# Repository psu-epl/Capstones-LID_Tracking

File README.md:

Capstones-LID_Tracking
------

###### This is the top level directory for the Capstone Awesome Usage Monitor project. The following repo directories contain the files used by this project and the developers to specify, design, and implement the project. This directory may be copied whole into any preconfigured Django AUM project instance. See below on how to configure and setup an AUM project instance.

---

* ./sm/ - Files associated with the Station Module. Not used by Django.
* ./aum/ - Django associated python files for the aum project and used by all applications.
* ./aumwi/ - Django associated python files for the web interface application.
* ./doc/ - Project Documentation, including User Manuals.
* ./static/ - css, js, img, and font files used by Django to render webpages, organized by project
* ./templates/registration/ - Django authentication and password management html files
* ./testing/ - Testing software and associated coverage results zip
* ./manage.py - Django management code.

---

The development environment for the Awesome Usage Monitor used an Ubuntu 16.04 server instance with python3.0 installed and running as a virtual environment.  The server was configured with SMTP, a postgreSQL database, Gunicorn application server, and Nginx setup as the webserver and the reverse proxy to Gunicorn.  Django 1.11 was used to develop the project.

---

The test environment was created using pytest and pytest-django for python3, for detailed instructions on how to create additional tests or verify the functionality of your production instance of the Awesome Usage Monitor please visit this [Pytest-Django Tutorial](http://pytest-django.readthedocs.io/en/latest/tutorial.html)

---

For detailed instructions on how to create a production environment similar to the development environment please visit this [DigitalOcean Tutorial](https://www.digitalocean.com/community/tutorials/how-to-set-up-django-with-postgres-nginx-and-gunicorn-on-ubuntu-16-04).

---

For detailed documentation on any Django function used within the project, please refer to the [Django 1.11 Documentation](https://docs.djangoproject.com/en/1.11/) or the [Django source code](https://github.com/django/django), both of which are extensive and extremely helpful.

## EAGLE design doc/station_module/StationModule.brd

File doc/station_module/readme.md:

## Station Module

[How to set up the module](Setup.md) (connect to the Wifi, set parameters, etc)

[Using the Module](use.md)

[Brief description of Hardware and pin assignments](pin.md)

[Bill of Materials](bom.md)

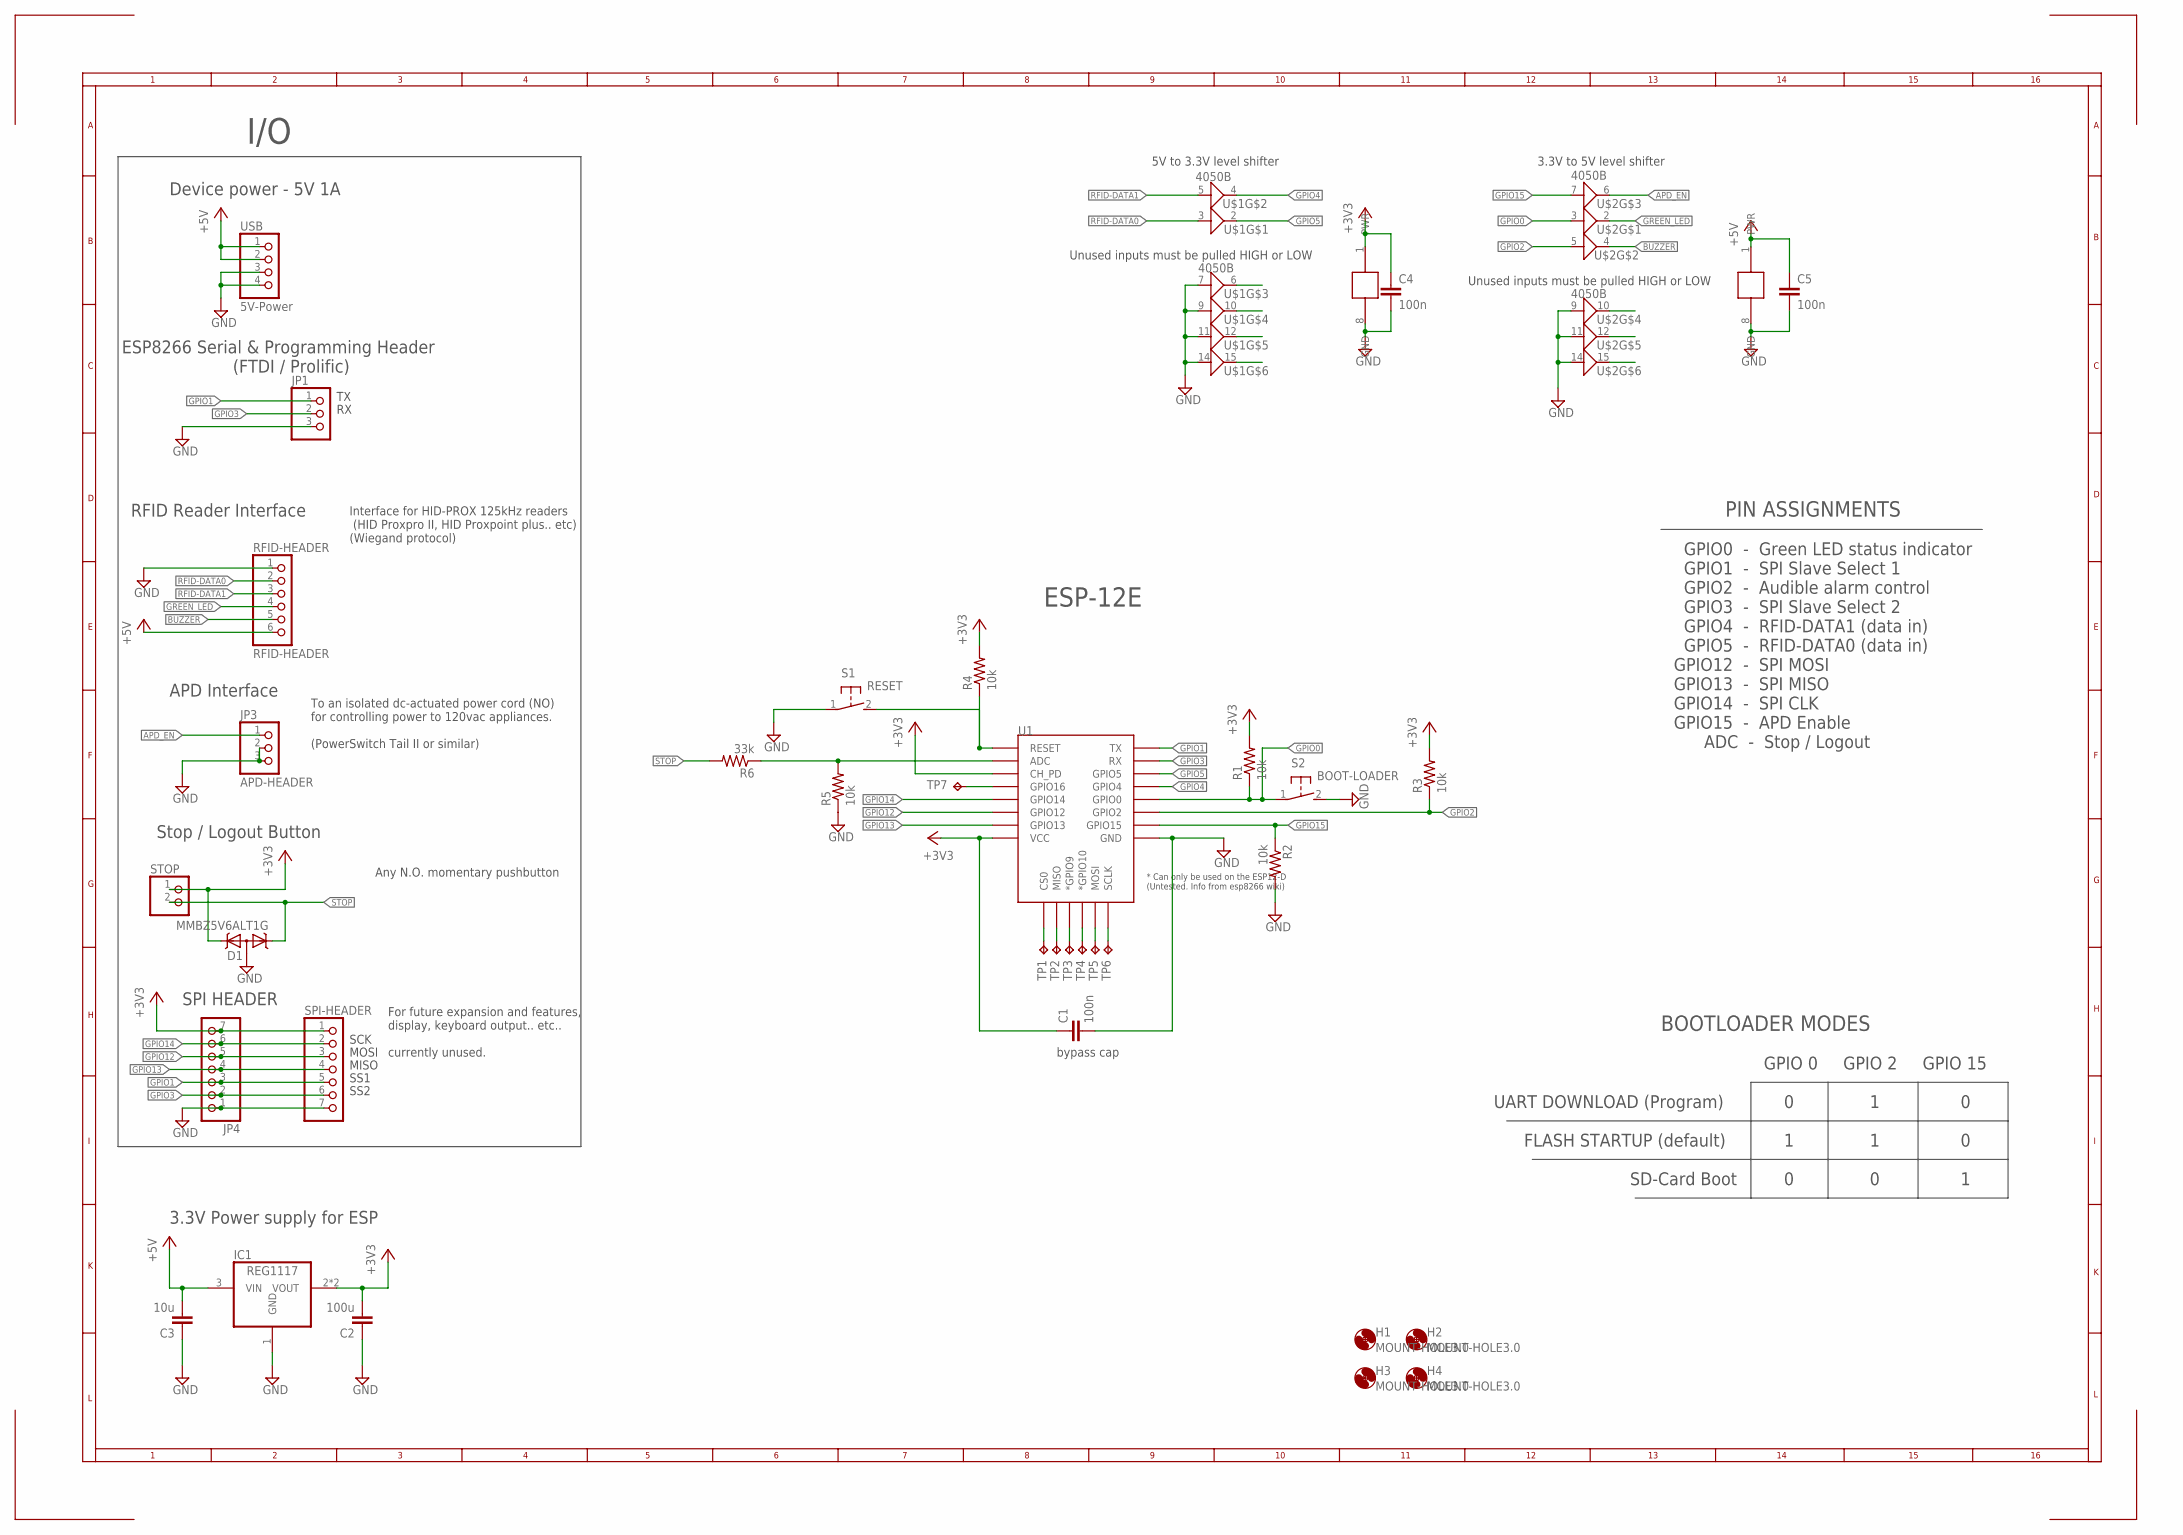
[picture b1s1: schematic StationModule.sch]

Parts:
C1, C4, C5: 100n; C0805K
C2: 100u; C0805K
C3: 10u; C0805K
D1: MMBZ5V6ALT1G; SOT23
H1, H2, H3, H4: MOUNT-HOLE3.0; 3,0
IC1: REG1117; SOT223
JP1: PINHD-1X3; 1X03
JP3: APD-HEADER; 1X03
JP4: PINHD-1X7; 1X07
R1, R2, R3, R4, R5: 10k; R0805
R6: 33k; R0805
RFID-HEADER: RFID-HEADER; 1X06
S1: RESET; DTSM-3
S2: BOOT-LOADER; DTSM-3
SPI-HEADER: PINHD-1X7; 1X07
STOP: PINHD-1X2; 1X02
TP1, TP2, TP3, TP4, TP5, TP6, TP7: TPB1,27; B1,27
U1: ESP12ESMD; ESP12E-SMD
U$1, U$2: 4050B; SOIC16N
USB: 5V-Power; 1X04

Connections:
+3V3: C1.1, C2.2, C4.1, D1.2 (K2), IC1.2 (VOUT), IC1.4 (VOUT), JP4.7, R1.2, R3.2, R4.2, SPI-HEADER.1, STOP.1, U1.CH_PD, U1.VCC, U$1.1 (PWR)
+5V: C3.2, C5.1, IC1.3 (VIN), RFID-HEADER.6, U$2.1 (PWR), USB.1, USB.2
ADC: R5.2, R6.1, U1.ADC
APD_EN: JP3.1, U$2.6
BUZZER: RFID-HEADER.5, U$2.4
GND: C1.2, C2.1, C3.1, C4.2, C5.2, D1.3 (AA), IC1.1 (GND), JP1.3, JP3.2, JP3.3, JP4.1, R2.2, R5.1, RFID-HEADER.1, S1.1, S2.2, SPI-HEADER.7, U1.GND, U$1.7, U$1.8 (GND), U$1.9, U$1.11, U$1.14, U$2.8 (GND), U$2.9, U$2.11, U$2.14, USB.3, USB.4
GPIO0: R1.1, S2.1, U1.GPIO0, U$2.3
GPIO1: JP1.1, JP4.3, SPI-HEADER.5, U1.TXD0 (TX)
GPIO2: R3.1, U1.GPIO2, U$2.5
GPIO3: JP1.2, JP4.2, SPI-HEADER.6, U1.RXD0 (RX)
GPIO4: U1.GPIO4, U$1.4
GPIO5: U1.GPIO5, U$1.2
GPIO12: JP4.5, SPI-HEADER.3, U1.GPIO12
GPIO13: JP4.4, SPI-HEADER.4, U1.GPIO13
GPIO14: JP4.6, SPI-HEADER.2, U1.GPIO14
GPIO15: R2.1, U1.GPIO15, U$2.7
GREEN_LED: RFID-HEADER.4, U$2.2
unnamed: TP7.TP, U1.GPIO16
unnamed: TP1.TP, U1.CS0
unnamed: TP2.TP, U1.MISO
unnamed: TP3.TP, U1.GPIO9 (*GPIO9)
unnamed: TP4.TP, U1.GPIO10 (*GPIO10)
unnamed: TP5.TP, U1.MOSI
unnamed: TP6.TP, U1.SCLK
RESET: R4.1, S1.2, U1.RESET
RFID-DATA0: RFID-HEADER.2, U$1.3
RFID-DATA1: RFID-HEADER.3, U$1.5
STOP: D1.1 (K1), R6.2, STOP.2

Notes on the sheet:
bypass cap
Device power - 5V 1A
I/O
ESP8266 Serial & Programming Header (FTDI / Prolific)
RFID Reader Interface
3.3V Power supply for ESP
ESP-12E
APD Interface
Unused inputs must be pulled HIGH or LOW
5V to 3.3V level shifter
3.3V to 5V level shifter
SPI HEADER
SS1
SS2
SCK
MOSI
MISO
Stop / Logout Button
BOOTLOADER MODES
GPIO 0 GPIO 2 GPIO 15 0 1 0 1 1 0 0 0 1
UART DOWNLOAD (Program) FLASH STARTUP (default) SD-Card Boot
GPIO0 - Green LED status indicator GPIO1 - SPI Slave Select 1 GPIO2 - Audible alarm control GPIO3 - SPI Slave Select 2 GPIO4 - RFID-DATA1 (data in) GPIO5 - RFID-DATA0 (data in) GPIO12 - SPI MOSI GPIO13 - SPI MISO GPIO14 - SPI CLK GPIO15 - APD Enable ADC - Stop / Logout
PIN ASSIGNMENTS
Interface for HID-PROX 125kHz readers (HID Proxpro II, HID Proxpoint plus.. etc) (Wiegand protocol)
Any N.O. momentary pushbutton
For future expansion and features, display, keyboard output.. etc.. currently unused.
To an isolated dc-actuated power cord (NO) for controlling power to 120vac appliances. (PowerSwitch Tail II or similar)

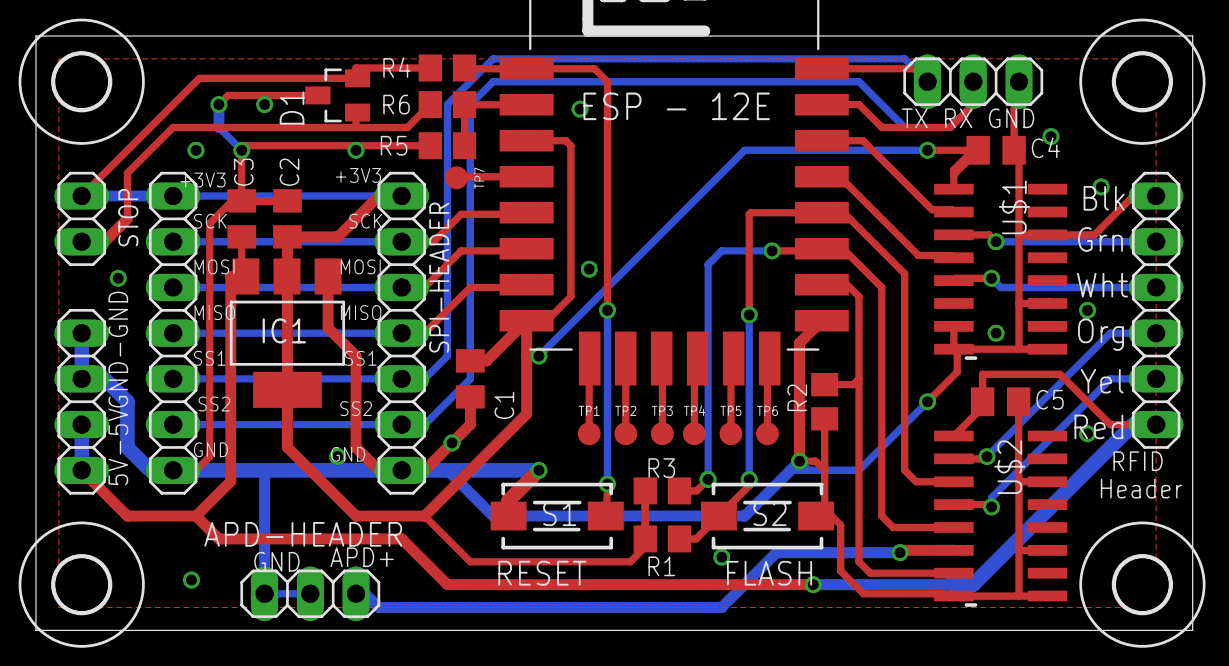
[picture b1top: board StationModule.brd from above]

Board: 2 copper layers, 64.3 x 33.0 mm, 36 parts (0 on the bottom side), 28 nets.

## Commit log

2017-01-12 initial commit
    file structure and READMEs
2017-01-12 initial commit part II
    more READMEs, and no double extensions
2017-01-13 Meeting Minutes 2017_01_11
    Initial meeting to begin fleshing out project proposal
2017-01-13 Meeting Minutes: 01/10/2017
    Impromptu meeting to help flesh out project proposal
2017-01-13 Meeting minutes: 01/12/2017
    Held a meeting with the advisor at 9am to go over draft project proposal and team structuring followed by a regular team meeting afterward. These notes document the follow-up to the advisor's directi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
2017-01-13 Meeting Minutes: 01/11/2017
    Held a meeting with the advisor at 9am to go over draft project proposal and team structuring followed by a regular team meeting afterward. These notes document the follow-up to the advisor's directi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
2017-01-19 WPR for end of 1/13/17
2017-01-27 Proposed Schedule
    Draft V1.2 of the Proposed Schedule
2017-01-30 updates schedule
2017-01-30 correct schedule
2017-02-06 Add files via upload
    added WPRs
2017-02-06 Add files via upload
    added PDS
2017-02-08 Database Additions
    Relational Diagrams v1.0
2017-02-08 Database Planning
    Entity Relationship Diagrams for Database tables
2017-02-08 Add Readme
2017-02-15 Updated SM HW stuff
2017-02-15 Started live design docu
2017-02-18 File Shuffling + WI Flow Chart
    I created folders to house the documents I was creating. Included in
    this upload is the Preliminary Web Flow Chart. Web Interface State
    Diagram pending.
2017-02-20 Documentation Upload
    More Documentation, as well as additional file restructure.
2017-02-24 Training Tutorial
    this is all the files from the training tutorial we have been working with. These files go from part1-part4. part 5 is testing and there are 7 parts to the whole tutorial.
2017-02-24 Project Files for implementing Users, Tool, and their interactions.
    These file are the tutorial in the training section that have now been modified to add Users, Tools, and Tool_Users. The next step is to write views for them all and figure out how to do logs of punc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
2017-03-08 Use Cases: database & web framwork V1.1
2017-03-10 Station module schematic
2017-03-10 linked datasheets
2017-03-10 update gitignore
    ignore backup files
2017-03-17 Add files via upload
    Use Cases: database & web framework V1.2
2017-03-24 current working stuff
    newer
2017-03-24 Rebased File System
    Moved recent changes into correct file structures and renamed web
    interface folders to correspond with maturing project.
2017-03-27 removed Questions and Choices, modified punches
    questions and choices have been commented out but are still there, just
    in case.
    Punches has been modified to act correctly.
2017-04-10 Updated SM
2017-04-10 SM rev1
2017-04-10 SM revision 1
2017-04-11 silkscreen
2017-04-14 sm readme
2017-04-14 Schematic annotation
2017-04-14 Uploaded BOM to SM readme
2017-04-22 New Files from Server
2017-05-01 this is done
2017-05-05 SM v1.1
    with fixes
2017-05-05 updated sch
    labeling conventions from andrew
2017-05-05 sm board
    moist current one
2017-06-05 working station module firmware
    still has hardcoded SMID :(
2017-06-15 added "double tap" feature to add users
2017-06-16 AUM Django Test Document
2017-06-16 Testing: AUM settings folder
2017-06-16 Testing: AUM virtual environment
2017-06-16 Testing: AUM "aumwi" app
    Contains directory of tests written for aumwi app.
2017-06-16 Testing: Coverage reports
    Houses callable index file to view reports.
2017-06-16 Tutorial on testing in Django that was pretty rad.
2017-06-16 Testing: AUM manage.py file
2017-06-16 Testing: pytest instructions file
2017-06-16 removing aumenv
    Beginning of aumenv cleanup. 100/5994 changes.
2017-06-16 rebase cont
    ?/5884
2017-06-16 rebase cont
    ?/5777
2017-06-16 rebase cont
    ?/5658
2017-06-16 rebase cont
    ?/5559
2017-06-16 rebase cont
    ?/5399
2017-06-16 crazy rebase
    attempt to just do all 5232 changes
2017-06-16 Testing: AUM settings folder files
    Uploaded 2 hours ago. Folder went missing. Re-uploaded.
2017-06-16 Testing: Virtual environment
    Uploaded two houes ago. zip folder fils went missing. Re-upload.
2017-06-16 Testing: AUM "aumwi" app. ***TESTS LIVE IN HERE
    Uploaded two hours ago. Folder files went missing. Re-upload.
2017-06-16 no but seriously
    I'm rebasing here!
2017-06-16 precision rebase for jessica's tests
2017-06-17 JP deleted the last one
2017-06-17 Issues fixed
2017-06-17 pics for docu
2017-06-17 added img for read
2017-06-17 moved some stuff
2017-06-17 Delete StationModule.s#4
    should have been excluded, whoops
2017-06-19 Final Rebase
    Moved all documentation to the ./doc directory.
    Renamed all directories and files to be GNU compatible
    Added User Manual
    Added original html templates
